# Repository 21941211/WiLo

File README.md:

# WiLo
Full documentation of the WiLo (Wireless Logger) LoRa enabled environmental monitoring logger.

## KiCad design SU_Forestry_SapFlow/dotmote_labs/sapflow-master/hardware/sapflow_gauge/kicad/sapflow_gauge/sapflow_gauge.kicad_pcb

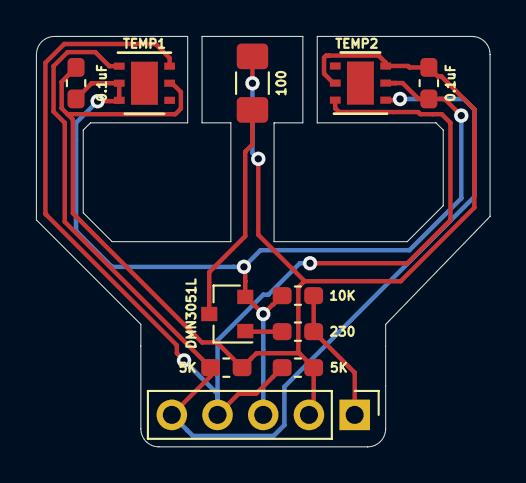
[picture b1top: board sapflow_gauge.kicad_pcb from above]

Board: 2 copper layers, 25.2 x 22.8 mm, 11 parts (0 on the bottom side), 7 nets.

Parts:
0.1uF, 0.1uF#2: 0.1uF; C_0603_1608Metric_Pad1.05x0.95mm_HandSolder
5K, 5K#2: 5K; R_0603_1608Metric_Pad1.05x0.95mm_HandSolder
10K: 10K; R_0603_1608Metric_Pad1.05x0.95mm_HandSolder
100: 100; R_1206_3216Metric_Pad1.42x1.75mm_HandSolder
230: 230; R_0603_1608Metric_Pad1.05x0.95mm_HandSolder
 : Conn_01x05_Female; PinHeader_1x05_P2.54mm_Vertical
DMN3051L: DMN3051L; SOT-23
TEMP1, TEMP2: HDC2080; Texas_PWSON-N6

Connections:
+3V3: 0.1uF.1, 0.1uF#2.1, 5K.1, 5K#2.1, 100.2, .2, TEMP1.5, TEMP2.3, TEMP2.5
GND: 0.1uF.2, 0.1uF#2.2, 10K.1, .3, DMN3051L.2, TEMP1.2, TEMP1.3, TEMP2.2
unnamed: 10K.2, 230.1, .1
unnamed: 5K.2, .4, TEMP1.6, TEMP2.6
unnamed: 5K#2.2, .5, TEMP1.1, TEMP2.1
unnamed: 230.2, DMN3051L.1
unnamed: 100.1, DMN3051L.3

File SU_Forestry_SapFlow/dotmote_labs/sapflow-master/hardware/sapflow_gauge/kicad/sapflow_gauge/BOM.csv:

"Id";"Designator";"Footprint";"Quantity";"Designation";"Supplier and ref";
1;"0.1uF,0.1uF";"C_0603_1608Metric_Pad1.05x0.95mm_HandSolder";2;"0.1uF";;;
2;" ";"PinHeader_1x05_P2.54mm_Vertical";1;"Conn_01x05_Female";;;
3;"DMN3051L";"SOT-23";1;"DMN3051L";;;
4;"5K,5K";"R_0603_1608Metric_Pad1.05x0.95mm_HandSolder";2;"5K";;;
5;"230";"R_0603_1608Metric_Pad1.05x0.95mm_HandSolder";1;"230";;;
6;"10K";"R_0603_1608Metric_Pad1.05x0.95mm_HandSolder";1;"10K";;;
7;"TEMP2,TEMP1";"Texas_PWSON-N6";2;"HDC2080";;;
8;"100";"R_1206_3216Metric_Pad1.42x1.75mm_HandSolder";1;"100";;;

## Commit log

2025-04-16 WiLo Parameter file backups
    The files contained herein are text files, required by each WiLo in the IMPACT OAL deployment.
    you will see for each WiLo number (WiLo-xxx) there is a folder containing the LoRa keys. These need to be transferred to the SD card of each WiLo for LoRa integration. Ensure that SD cards are format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
2025-04-16 Inital Source Commit
2025-04-16 Test
2025-04-16 Another test
2025-04-16 OTA Firmware upgrade code added
2025-04-16 Added More Documentation
2025-04-17 Fixed OTA bugs, fixed deep sleep bugs
2025-04-21 payload formatter backup
2025-04-23 Added a firware extraction script
2025-04-29 OTA SoftAP and SF error flags
2025-05-02 Added datasheet
2025-05-02 Updated payload formatter
2025-05-05 Update LICENSE
2025-07-03 Updated folder structure
2025-07-03 Added Eagle source, gerber, BOM and centroid files for WiLoV2
2025-07-03 Updated DigiDendro, created PCB manufacturing files
2025-07-07 Updated WiLoV2 source code and PCBWay files
2025-08-04 Added WiLo V2 dcumentation
2025-09-05 rtc code uncommented and data timestamped before SD write
2025-11-14 MUX RTC fixes, SDI-12 bug fixes
2025-11-14 WiFi re-enabled, firmware.bin updated
2026-04-23 Added sapflow timer between heatpulse and after heatpulse measurements
2026-04-23 Added sapflow delay to WiLo V2
2026-04-24 Bug fixes
2026-04-24 Added flags for checking sapflow calculations
2026-04-24 Syntax error fix
2026-04-24 SDI-12 tests
2026-05-05 Sapflow Driver Fixes, one-shot measurement mode instead of continuous.
2026-05-26 Added longer rise time delay for sapflow measurements, reduced number of samples taken
2026-05-26 Fixed not printing count T2 after to serial
2026-05-29 Fixed some typos in serial debug
2026-06-23 Bug fixes for Mux overflow
